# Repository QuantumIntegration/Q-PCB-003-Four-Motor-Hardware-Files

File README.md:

# Quantum DIY Kit Hardware Files - Four Motor
## Introduction

This repository contains all the hardware files necessary to build the PCBs and assemble the DIY kits. The PCBs can be ordered from for example [JLCPCB](https://jlcpcb.com/) or [PCBWay](https://www.pcbway.com/). The components can be sourced mostly from [Amazon](https://amazon.com/) or [Digikey](https://digikey.com/), according to the links in the BOM file.

## Download the correct revision

If you are nor familiar with the git version control system, please follow these simple steps to download your version of the DIY kit

<em>1. Click the branch button</em>

<em>2. Select the branch matching your revision</em>

<em>3. Click the Code button</em>

<em>4. Download the ZIP and extract it on your machine</em>

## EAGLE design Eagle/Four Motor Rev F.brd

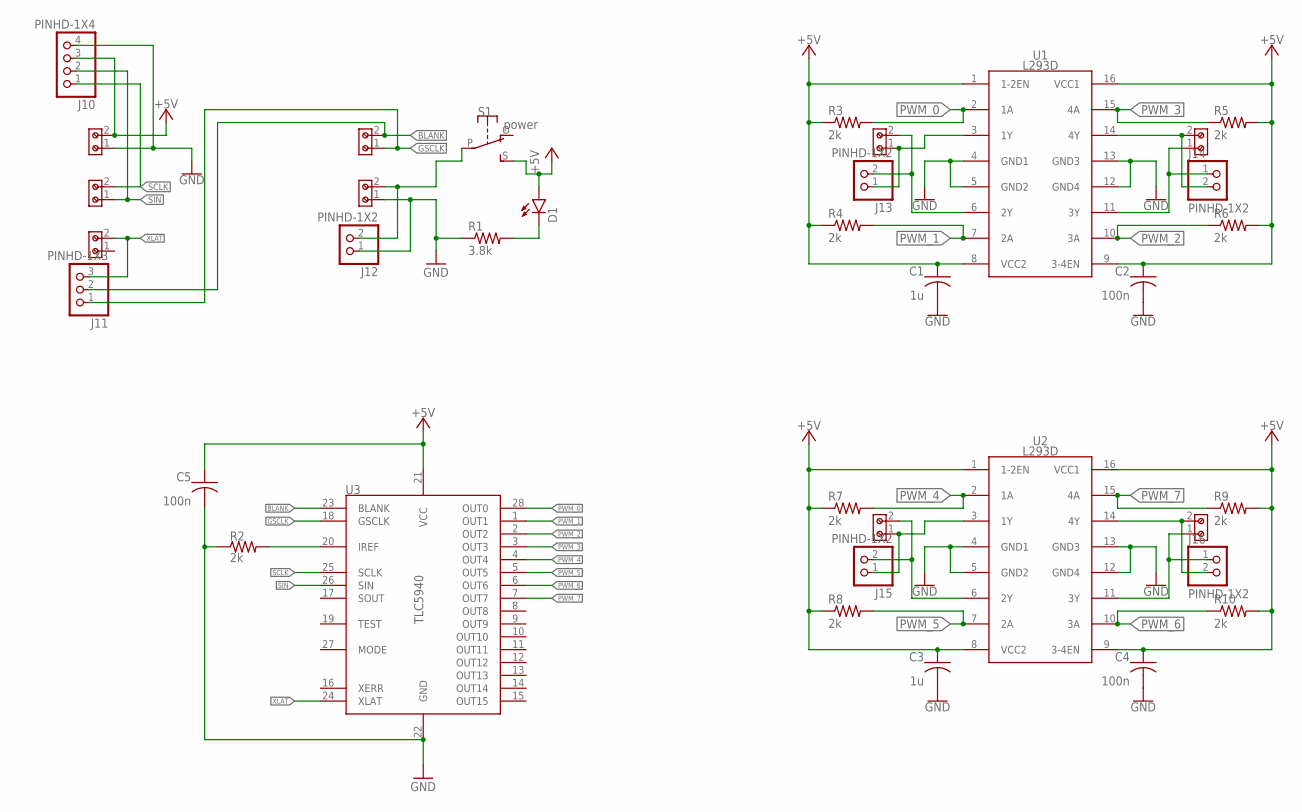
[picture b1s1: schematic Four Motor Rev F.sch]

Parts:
C1, C3: 1u; C050-024X044
C2, C4, C5: 100n; C050-024X044
D1: LED; LED5MM
J1, J2, J3, J4, J5, J6, J7, J8, J9: 691214110002
J10: PINHD-1X4; 1X04
J11: PINHD-1X3; 1X03
J12, J13, J14, J15, J16: PINHD-1X2; 1X02
R1: 3.8k; 0207/10
R2, R3, R4, R5, R6, R7, R8, R9, R10: 2k; 0207/10
S1: power; EG1270-90
U1, U2: L293D; DIL16
U3: TLC5940; DIL28-3

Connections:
+5V: C1.1, C2.1, C3.1, C4.1, C5.1, D1.A, J6.2, J10.3, R3.1, R4.1, R5.2, R6.2, R7.1, R8.1, R9.2, R10.2, S1.S, U1.1 (1-2EN), U1.8 (VCC2), U1.9 (3-4EN), U1.16 (VCC1), U2.1 (1-2EN), U2.8 (VCC2), U2.9 (3-4EN), U2.16 (VCC1), U3.21 (VCC)
BLANK: J9.2, J11.2, U3.23 (BLANK)
GND: C1.2, C2.2, C3.2, C4.2, C5.2, J1.1, J6.1, J10.4, J12.1, R1.1, R2.1, U1.4 (GND1), U1.5 (GND2), U1.12 (GND4), U1.13 (GND3), U2.4 (GND1), U2.5 (GND2), U2.12 (GND4), U2.13 (GND3), U3.22 (GND)
GSCLK: J9.1, J11.1, U3.18 (GSCLK)
unnamed: J4.1, J15.1, U2.3 (1Y)
unnamed: J4.2, J15.2, U2.6 (2Y)
unnamed: J1.2, J12.2, S1.P
unnamed: J5.2, J13.2, U1.6 (2Y)
unnamed: J2.2, J14.2, U1.14 (4Y)
unnamed: J2.1, J14.1, U1.11 (3Y)
unnamed: J3.2, J16.2, U2.14 (4Y)
unnamed: J3.1, J16.1, U2.11 (3Y)
unnamed: J5.1, J13.1, U1.3 (1Y)
unnamed: D1.K (C), R1.2
unnamed: R2.2, U3.20 (IREF)
PWM_0: R3.2, U1.2 (1A), U3.28 (OUT0)
PWM_1: R4.2, U1.7 (2A), U3.1 (OUT1)
PWM_2: R6.1, U1.10 (3A), U3.2 (OUT2)
PWM_3: R5.1, U1.15 (4A), U3.3 (OUT3)
PWM_4: R7.2, U2.2 (1A), U3.4 (OUT4)
PWM_5: R8.2, U2.7 (2A), U3.5 (OUT5)
PWM_6: R10.1, U2.10 (3A), U3.6 (OUT6)
PWM_7: R9.1, U2.15 (4A), U3.7 (OUT7)
SCLK: J7.2, J10.1, U3.25 (SCLK)
SIN: J7.1, J10.2, U3.26 (SIN)
XLAT: J8.2, J11.3, U3.24 (XLAT)

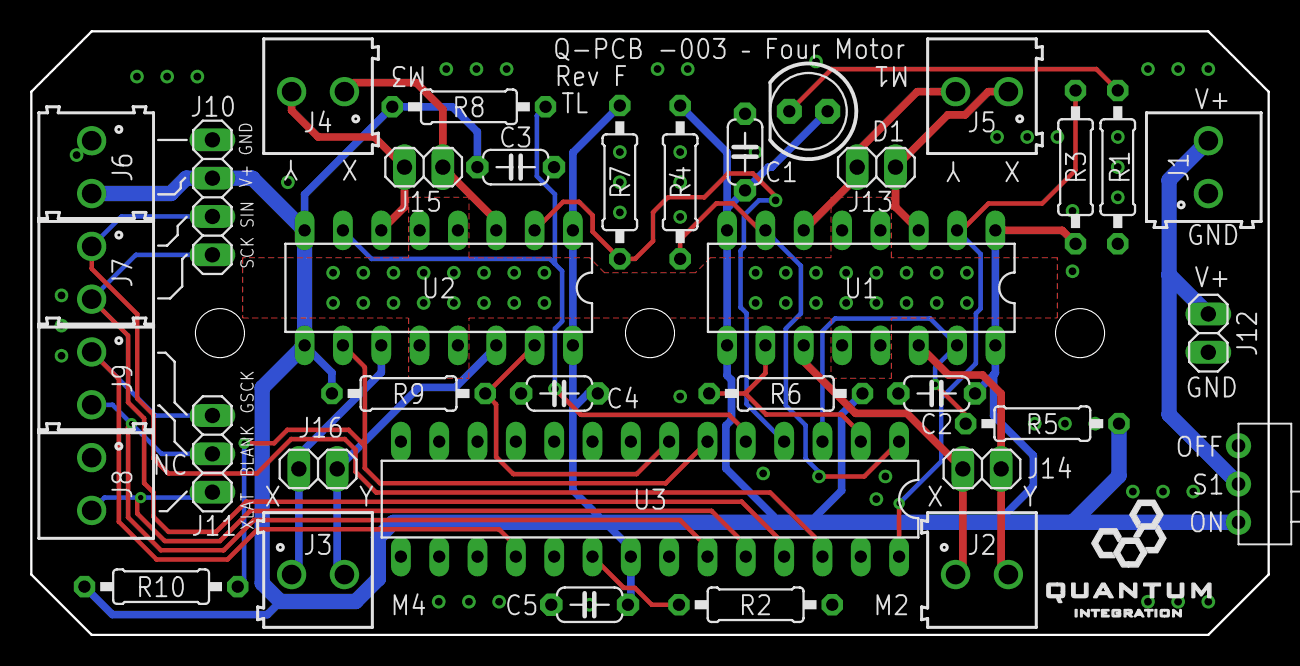
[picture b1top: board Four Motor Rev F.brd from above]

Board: 2 copper layers, 82.0 x 40.0 mm, 36 parts (0 on the bottom side), 26 nets.

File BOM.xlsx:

Index | Part | Value | Quantity | Designators | Package | Comments | Specific Part Reference | Part Link Example
1 | Terminal |  | 9 | J1, J2, J3, J4, J5, J6, J7, J8, J9 |  | 3.50mm, 1x2 |  | https://www.digikey.com/product-detail/en/w%C3%BCrth-elektro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
2 | TLC5940 |  | 1 | U3 | DIP-28 |  |  | https://www.digikey.com/en/products/detail/texas-instruments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
3 | Slide Switch |  | 1 | S1 |  | 90 degree | EG1270 | https://www.digikey.com/product-detail/en/e-switch/EG1270/EG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
4 | Ceramic Capacitor | 100n | 3 | C2, C4, C5 | 024x044 |  |  | https://www.digikey.com/en/products/detail/kemet/C315C104M5U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
5 | Ceramic Capacitor | 1u | 2 | C1, C3 | 024x044 |  |  | https://www.digikey.com/en/products/detail/kemet/C330C105K5R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
6 | L293D |  | 2 | U1, U2 | DIP-14 |  |  | https://www.amazon.com/Organizer-16-pin-Stepper-Drivers-Cont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
7 | Resistor | 2k | 9 | R2, R3, R4, R5, R6, R7, R8, R8, R10 | 0207/10 | 1/4 W |  | https://www.amazon.com/SIQUK-Resistors-Resistor-Assortment-E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
8 | Resistor | 3.8k | 1 | R1 | 0207/10 | 1/4 W |  | https://www.amazon.com/SIQUK-Resistors-Resistor-Assortment-E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
9 | LED | green-diffused | 1 | D1 | 5mm |  |  | https://www.amazon.com/Diffused-Lighting-Electronics-Compone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
10 | Header |  | 5 | J12, J13, J14, J15, J16 | 0.1 | 1x2, male |  | https://www.amazon.com/MCIGICM-Header-2-45mm-Arduino-Connect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
11 | Header |  | 1 | J11 |  | 1x3, male |  | https://www.amazon.com/MCIGICM-Header-2-45mm-Arduino-Connect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
12 | Header |  | 1 | J10 |  | 1x4, male |  | https://www.amazon.com/MCIGICM-Header-2-45mm-Arduino-Connect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
13 | 14 pin carrier |  | 2
13 | 28 pin carrier |  | 1

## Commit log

2021-03-16 edited readme and gitignore
2021-03-16 added project content
2021-03-16 edited readme title
2021-03-16 added readme preview
2021-05-11 updated BOM resistor values
2021-05-17 added Arduino files
2021-08-17 added schematic as PDF

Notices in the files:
parts and their libraries:
Wurth_Connectors_WR-TBL Rising Cage Clam: Copyright: Würth Elektronik
